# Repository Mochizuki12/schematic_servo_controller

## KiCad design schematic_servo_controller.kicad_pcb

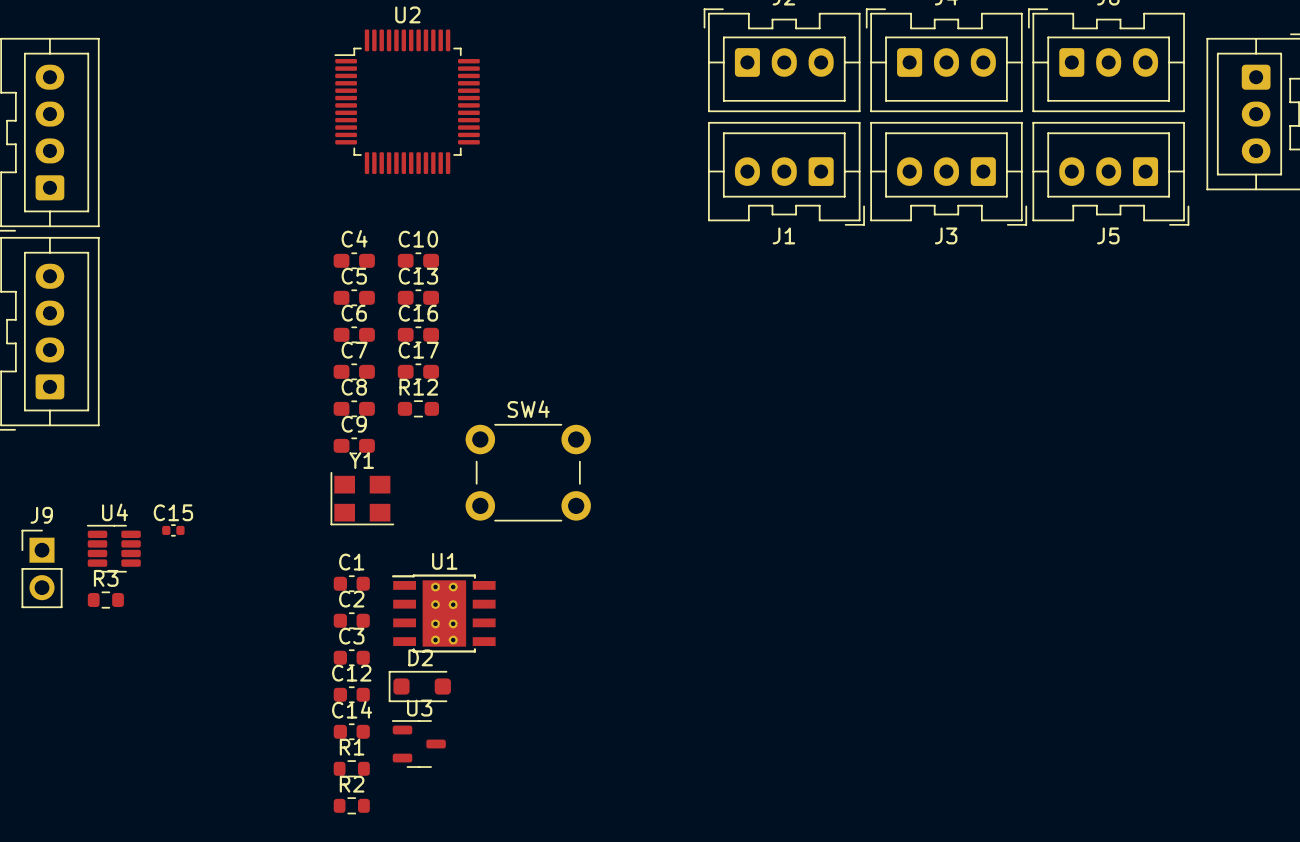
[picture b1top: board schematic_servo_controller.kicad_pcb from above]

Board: 2 copper layers, 37 parts (0 on the bottom side), 17 nets, no tracks yet.

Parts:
C1, C2: 4.7uF; C_0603_1608Metric
C3: 0.01uF; C_0603_1608Metric
C4, C8, C9, C10, C13, C17: 0.1uF; C_0603_1608Metric_Pad1.08x0.95mm_HandSolder
C5, C6: 10pF; C_0603_1608Metric_Pad1.08x0.95mm_HandSolder
C7, C16: 10uF; C_0603_1608Metric_Pad1.08x0.95mm_HandSolder
C12, C14: 1uF; C_0603_1608Metric
C15: 0.1u; C_0402_1005Metric
D2: D_Schottky; D_SOD-123F
J1, J2, J3, J4, J5, J6, J7: Conn_01x03; JST_XA_B03B-XASK-1_1x03_P2.50mm_Vertical
J8, J10: Conn_01x04; JST_XA_B04B-XASK-1_1x04_P2.50mm_Vertical
J9: Conn_02x01; PinHeader_1x02_P2.54mm_Vertical
R1: 12k; R_0603_1608Metric
R2: 3.9k; R_0603_1608Metric
R3: 120; R_0603_1608Metric
R12: 10k; R_0603_1608Metric_Pad0.98x0.95mm_HandSolder
SW4: SW_SPST; SW_PUSH_6mm_H7.3mm
U1: TPS5430DDA; TI_SO-PowerPAD-8_ThermalVias
U2: STM32F103CBTx; LQFP-48_7x7mm_P0.5mm
U3: XC6206P332MR-G; SOT-23-3
U4: MAX3051; SOT-23-8
Y1: 12MHz; Crystal_SMD_SeikoEpson_FA238V-4Pin_3.2x2.5mm

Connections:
+3.3V: C14.1, C15.1, D2.2 (A), U3.2 (VO), U4.3 (VDD)
+5V: C12.1, D2.1 (K), R1.1, U3.3 (VI)
+7.5V: J1.2, J2.2, J3.2, J4.2, J5.2, J6.2, J7.2
+12V: C1.1, C2.1, J8.2, J10.2, U1.7 (VIN)
GND: C1.2, C2.2, C4.2, C5.2, C6.2, C7.2, C8.2, C9.2, C10.2, C12.2, C13.2, C14.2, C15.2, C16.2, C17.2, J8.1, J10.1, R2.2, R12.2, SW4.1 (A), U1.6 (GND), U1.9 (GNDPAD), U2.8 (VSSA), U2.23 (VSS), U2.35 (VSS), U2.47 (VSS), U3.1 (GND), U4.2 (GND), U4.8 (RS), Y1.2, Y1.4
GNDPWR: J1.1, J2.1, J3.1, J4.1, J5.1, J6.1, J7.1
unnamed: C3.2, U1.8 (PH)
unnamed: J9.2, R3.1
unnamed: J8.3, J10.3, R3.2, U4.7 (CANH)
unnamed: J8.4, J9.1, J10.4, U4.6 (CANL)
unnamed: C4.1, SW4.2 (B), U2.7 (NRST)
unnamed: C3.1, U1.1 (BOOT)
unnamed: R1.2, R2.1, U1.4 (VSENSE)
unnamed: R12.1, U2.44 (BOOT0)
unnamed: C6.1, U2.5 (PD0), Y1.3
unnamed: C5.1, U2.6 (PD1), Y1.1
VDD: C7.1, C8.1, C9.1, C10.1, C13.1, C16.1, C17.1, U2.1 (VBAT), U2.9 (VDDA), U2.24 (VDD), U2.36 (VDD), U2.48 (VDD)

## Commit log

2025-04-15 change DCDC
